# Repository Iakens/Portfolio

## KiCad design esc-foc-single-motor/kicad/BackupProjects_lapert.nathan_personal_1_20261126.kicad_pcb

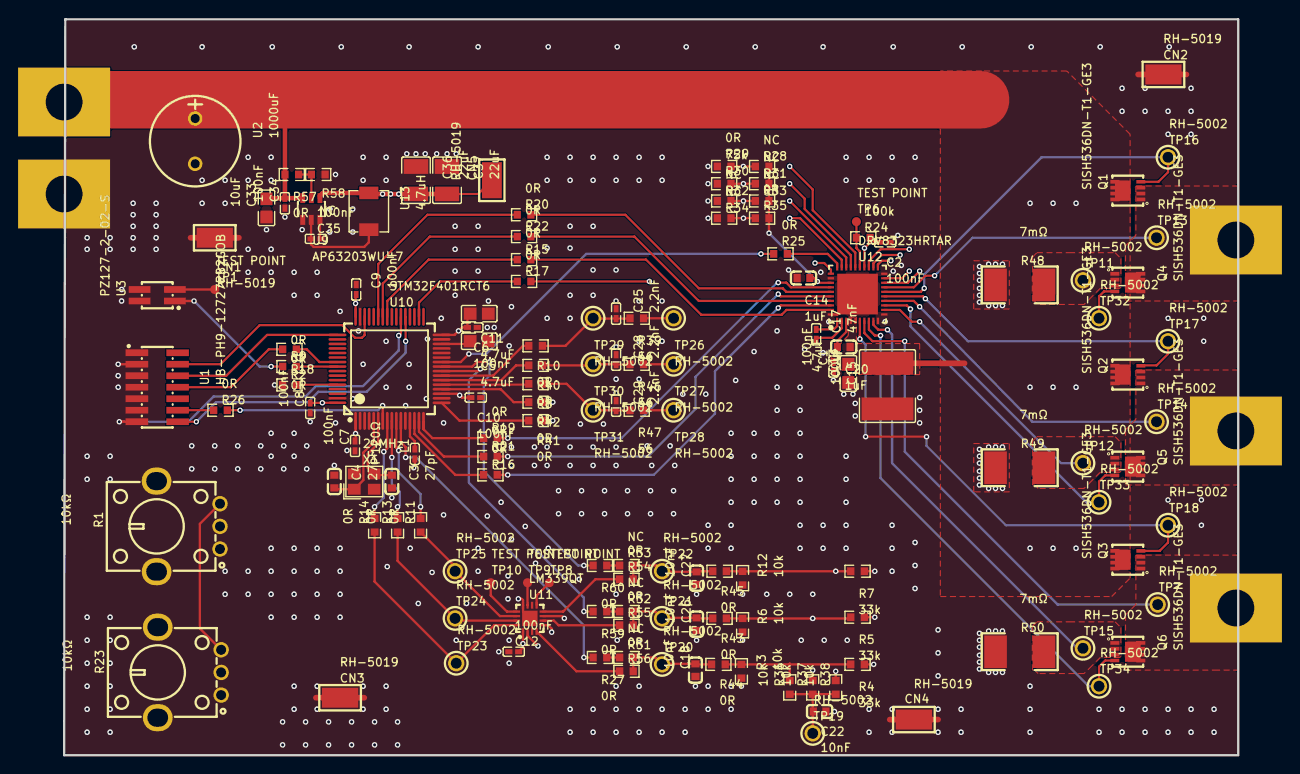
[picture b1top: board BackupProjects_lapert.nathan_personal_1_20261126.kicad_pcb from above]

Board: 4 copper layers, 129.7 x 81.3 mm, 145 parts (0 on the bottom side), 97 nets.

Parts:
C1, C2, C6, C7, C8, C9, C10, C12, C34, C35: 100nF; C0402
C3, C4: 27pF; C0603
C5, C11, C13: 4.7uF; C0805
C14, C20: 1uF; C0603
C15: 100uF; CAP-SMD_L6.1-W5.3
C17: 47nF; C0402
C18, C22, C26, C27: 10nF; C0603
C25, C28, C29: 2.2nF; C0402
C33: 10uF; C0805
C36, C37: 22uF; C1210
CN1, CN2, CN3, CN4, CN5: RH-5019; TESTPOINT-SMD_L3.8-W2.0_RH-5019
L1: 120Ω; L0402
Pad_gge105395: Pad_gge105395
Pad_gge105398: Pad_gge105398
Pad_gge105401: Pad_gge105401
Pad_gge105404: Pad_gge105404
Pad_gge105407: Pad_gge105407
Q1, Q2, Q3, Q4, Q5, Q6: SISH536DN-T1-GE3; POWERPAK-1212-8_L3.3-W3.3-P0.65-BL-EP
R1, R23: 10kΩ; RES-TH_RK09K113004U
R2, R8, R9, R10, R11, R13, R14, R15, R16, R17, R18, R19, R20, R21, R22, R25, R26, R27, R29, R35, R40, R41, R42, R43, R44, R45, R54, R55, R56, R57, R59, R60: 0R; R0603
R3, R6, R12, R36, R37, R38: 10k; R0603
R4, R5, R7: 33k; R0603
R24: 100k; R0603
R28, R31, R32, R33, R34, R51, R52, R53, R58: NC; R0603
R30: 75k; R0603
R39, R46, R47: 56; R0603
R48, R49, R50: 7mΩ; RES-SMD_L6.4-W3.2_LR2512D-3W-1MR
TP1, TP6, TP8, TP9, TP10: TEST POINT; TESTPOINT
TP7, TP11, TP12, TP13, TP14, TP15, TP16, TP17, TP18, TP19, TP20, TP21, TP22, TP23, TP24, TP25, TP26, TP27, TP28, TP29, TP30, TP31, TP32, TP33, TP34: RH-5002; TESTPOINT_TH_BD2.5-D1.2
U1: HB-PH9-12727PB2GOB; HDR-SMD_14P-P1.27-V-M-R2-C7-LS5.5
U2: 1000uF; CAP-TH_BD10.0-P5.00-D0.6-FD
U3: PZ127-2-02-S; HDR-SMD_4P-P1.27-V-M-R2-C2-LS5.3
U9: AP63203WU-7; TSOT-26_L2.9-W1.6-P0.95-LS2.8-BL
U10: STM32F401RCT6; LQFP-64_L10.0-W10.0-P0.50-LS12.0-BL
U11: LM339QT; TQFN-16_L3.0-W3.0-P0.50-BL-EP1.7
U12: DRV8323HRTAR; QFN-40_L6.0-W6.0-P0.50-BL-EP4.5
U13: 4.7uH; IND-SMD_L4.4-W4.2
X1: 24MHz; CRYSTAL-SMD_4P-L3.2-W2.5-BL

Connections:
3.3VNUM: C2.2, C6.2, C7.2, C8.2, C9.2, C10.2, C11.2, C12.2, C36.2, C37.2, CN5.1, L1.1, R1.3, R23.3, R24.2, U1.3, U9.1, U10.1, U10.19, U10.32, U10.48, U10.64, U11.1, U12.24, U13.2
+12V: C1.2, C13.2, C15.2, C20.1, C33.2, C34.2, Pad_gge105395.1, Q1.5, Q1.6, Q1.7, Q1.8, Q1.9, Q2.5, Q2.6, Q2.7, Q2.8, Q2.9, Q3.5, Q3.6, Q3.7, Q3.8, Q3.9, R57.2, U2.1, U9.3, U12.4, U12.5
AH: Q3.4, TP18.1, U12.6
AL: Q6.4, TP34.1, U12.8
BH: Q2.4, TP17.1, U12.15
BL: Q5.4, TP33.1, U12.13
C5_2: C5.2, U10.30
C17_1: C17.1, U12.1
C17_2: C17.2, U12.2
CAL: R17.2, U12.31
CH: Q1.4, TP16.1, U12.16
CL: Q4.4, TP32.1, U12.18
DVDD: C14.1, R28.2, R31.2, R33.2, R35.2, U12.33
EN_DRIVER: R25.2, U12.30
GAIN: R34.2, R35.1, U12.29
GND: C1.1, C2.1, C3.2, C4.1, C5.1, C6.1, C7.1, C8.1, C9.1, C10.1, C11.1, C12.1, C13.1, C14.2, C15.1, C18.1, C22.1, C25.1, C26.1, C27.1, C28.1, C29.1, C33.1, C34.1, C36.1, C37.1, CN1.1, CN2.1, CN3.1, CN4.1, Pad_gge105398.1, R1.1, R1.4, R1.5, R2.1, R3.2, R6.2, R12.2, R23.1, R23.4, R23.5, R29.1, R30.1, R32.1, R34.1, R48.1, R49.1, R50.1, R58.1, U1.5, U1.7, U2.2, U3.2, U3.4, U9.4, U10.12, U10.18, U10.31, U10.47, U10.63, U11.12, U11.17, U12.10, U12.11, U12.20, U12.32, U12.40, U12.41
IDRIVE: R30.2, R31.1, U12.27
INHA: R19.2, U12.34
INHB: R21.2, U12.36
INHC: R16.2, U12.38
INLA: R20.2, U12.35
INLB: R22.2, U12.37
INLC: R15.2, U12.39
INPUT_PWM: R9.1, U3.1
ISENA: C25.2, R10.1, R39.2, TP29.1
ISENB: C28.2, R40.1, R46.2, TP30.1
ISENC: C29.2, R8.1, R47.2, TP31.1
L1_2: L1.2, U10.13
MODE: R28.1, R29.2, U12.26
NRST: R26.1, U1.12
PHASE_1: Pad_gge105401.1, Q3.1, Q3.2, Q3.3, Q6.5, Q6.6, Q6.7, Q6.8, Q6.9, R4.1, TP7.1, U12.7
PHASE_2: Pad_gge105404.1, Q2.1, Q2.2, Q2.3, Q5.5, Q5.6, Q5.7, Q5.8, Q5.9, R5.1, TP14.1, U12.14
PHASE_3: Pad_gge105407.1, Q1.1, Q1.2, Q1.3, Q4.5, Q4.6, Q4.7, Q4.8, Q4.9, R7.1, TP13.1, U12.17
POTAR_1: R1.2, R42.1
POTAR_2: R23.2, R41.1
R2_2: R2.2, U10.60
R8_2: R8.2, U10.21
R9_2: R9.2, U10.56
R10_2: R10.2, U10.23
R11_2: R11.2, U10.10
R13_2: R13.2, U10.9
R14_2: R14.2, U10.8
R15_1: R15.1, U10.41
R16_1: R16.1, U10.14
R17_1: R17.1, U10.34
R18_1: R18.1, U10.55
R19_1: R19.1, U10.16
R20_1: R20.1, U10.43
R21_1: R21.1, U10.15
R22_1: R22.1, U10.42
R24_1: R24.1, TP6.1, U12.25
R36_2: R3.1, R4.2, R36.2, R44.1
R37_2: R5.2, R6.1, R37.2, R43.1
R38_2: R7.2, R12.1, R38.2, R45.1
R58_2: R57.1, R58.2, U9.2
SHUNT_1: Q6.1, Q6.2, Q6.3, R50.2, TP15.1, U12.9
SHUNT_2: Q5.1, Q5.2, Q5.3, R49.2, TP12.1, U12.12
SHUNT_3: Q4.1, Q4.2, Q4.3, R48.2, TP11.1, U12.19
SOA: R39.1, TP26.1, U12.23
SOB: R46.1, TP27.1, U12.22
SOC: R47.1, TP28.1, U12.21
SWCLK: U1.6, U10.49
SWDIO: U1.4, U10.46
SWO: R18.2, U1.8
TP8_1: TP8.1, U11.9
TP9_1: TP9.1, U11.11
TP10_1: TP10.1, U11.13
U3_3: TP1.1, U3.3
U9_6: C35.2, U9.6
U10_7: R26.2, U10.7
U10_11: R27.2, U10.11
U10_17: R41.2, U10.17
U10_20: R42.2, U10.20
U10_22: R40.2, U10.22
U10_24: R59.2, U10.24
U10_25: R60.2, U10.25
U10_26: R25.1, U10.26
U12_3: C20.2, U12.3
U13_1: C35.1, U9.5, U13.1
UART_RX: U1.13, U10.38
UART_TX: U1.14, U10.37
VDS: R32.2, R33.1, U12.28
VNP: C22.2, R36.1, R37.1, R38.1, TP19.1, U11.2, U11.5, U11.7
VSEN1: C18.2, R44.2, R51.2, R56.2, TP20.1
VSEN1_AOP: R56.1, U11.4
VSEN1_UC: R27.1, R51.1
VSEN2: C26.2, R43.2, R52.2, R55.2, TP21.1
VSEN2_AOP: R55.1, U11.6
VSEN2_UC: R52.1, R59.1
VSEN3: C27.2, R45.2, R53.2, R54.2, TP22.1
VSEN3_AOP: R54.1, U11.8
VSEN3_UC: R53.1, R60.1
X1_1: C4.2, U10.5, X1.1
X1_3: C3.1, U10.6, X1.3
ZCD_1: R14.1, TP23.1, U11.16
ZCD_2: R13.1, TP24.1, U11.15
ZCD_3: R11.1, TP25.1, U11.14
